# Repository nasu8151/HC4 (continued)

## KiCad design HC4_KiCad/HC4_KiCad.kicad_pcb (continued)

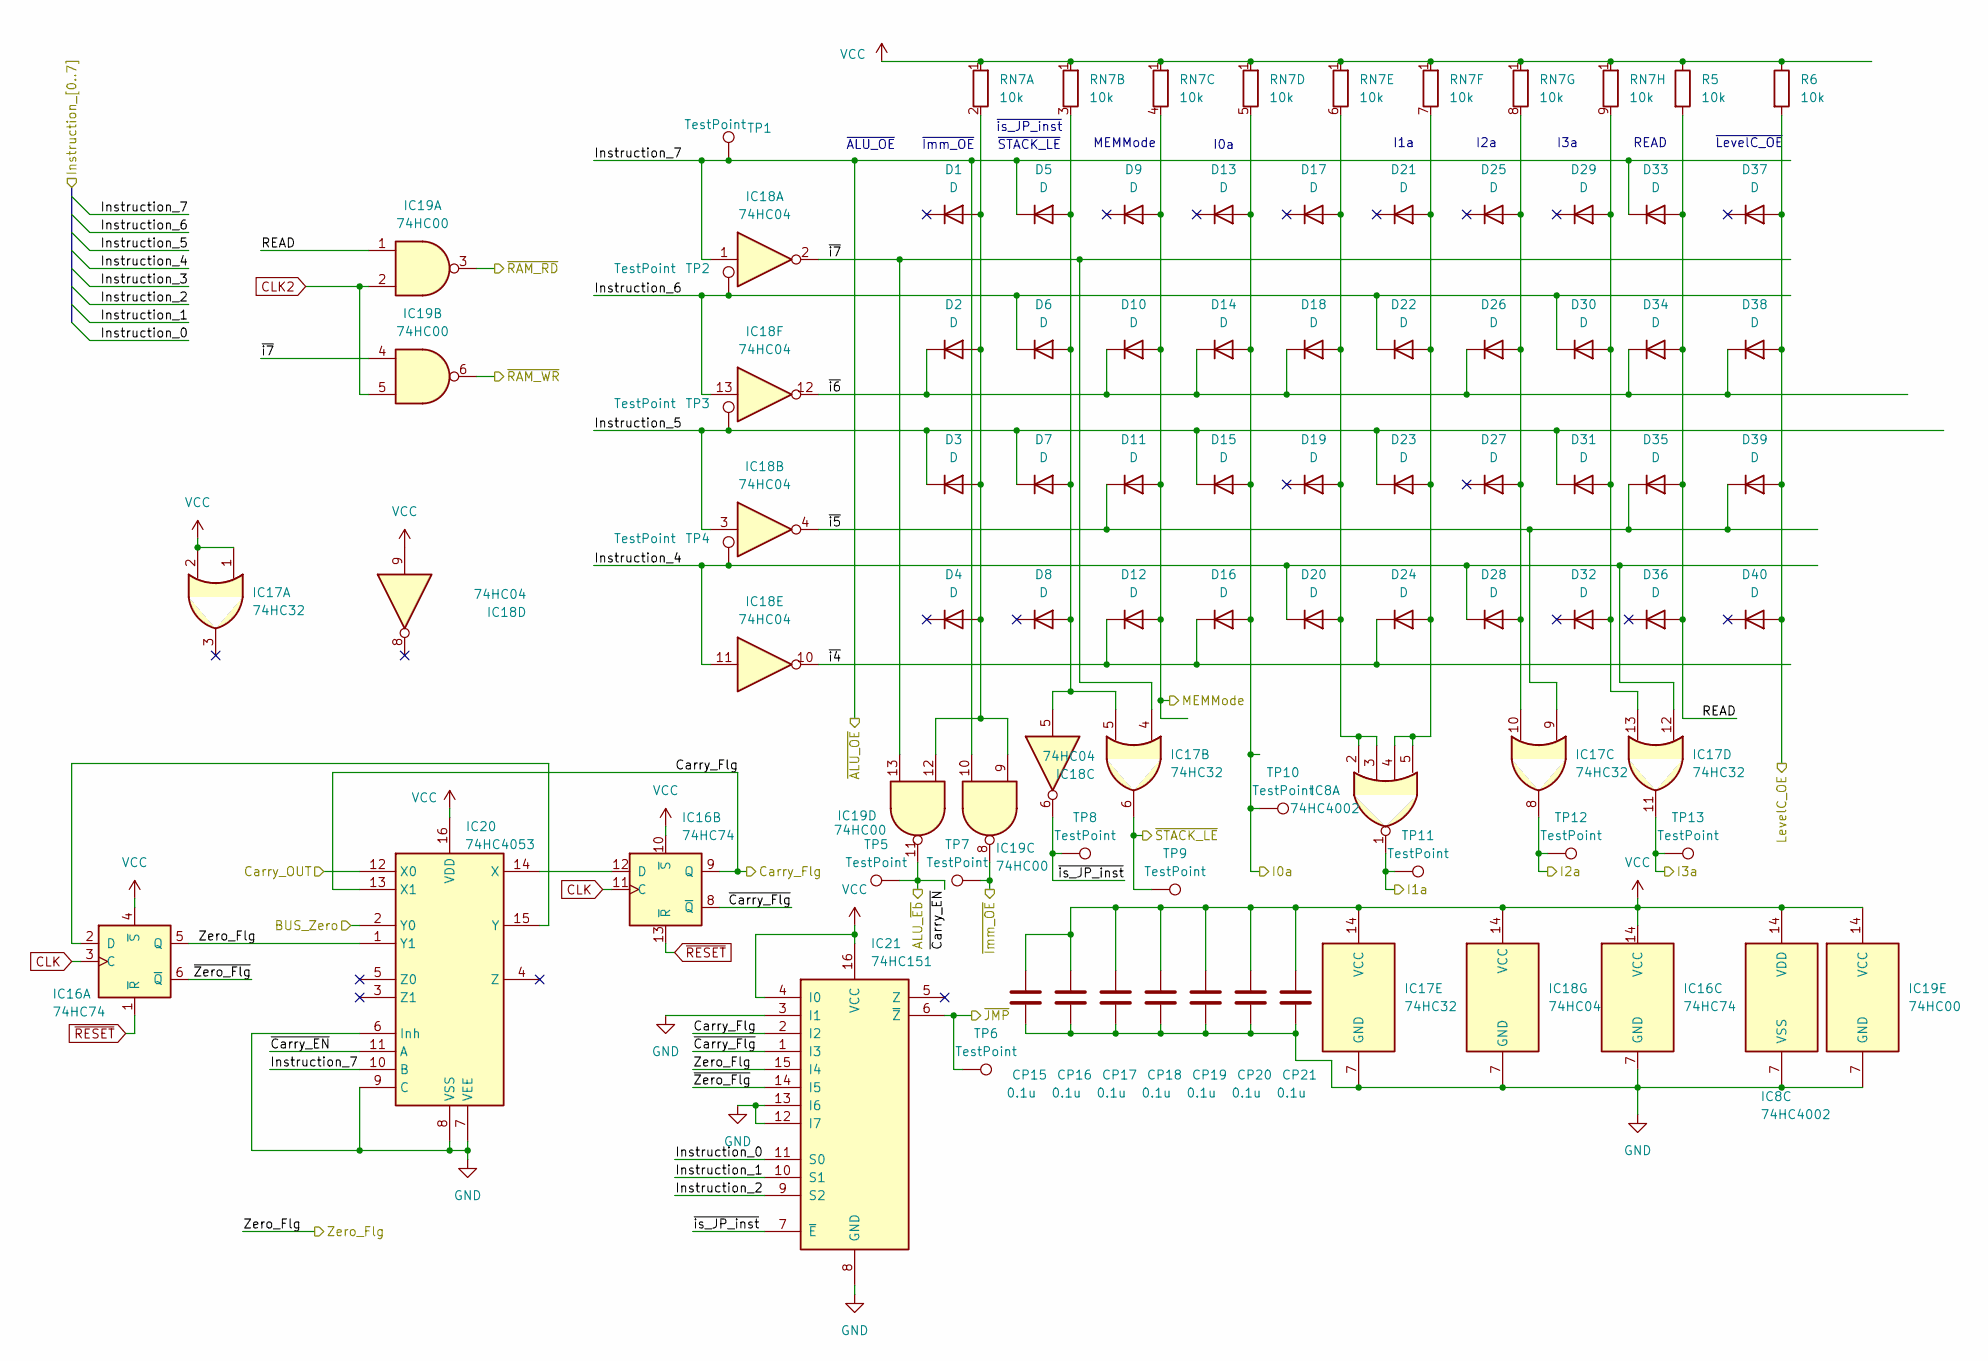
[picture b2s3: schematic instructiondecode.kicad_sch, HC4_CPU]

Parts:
CP15, CP16, CP17, CP18, CP19, CP20, CP21: 0.1u; C_0603_1608Metric
D1, D2, D3, D4, D5, D6, D7, D8, D9, D10, D11, D12, D13, D14, D15, D16, D17, D18, D19, D20, D21, D22, D23, D24, D25, D26, D27, D28, D29, D30, D31, D32, D33, D34, D35, D36, D37, D38, D39, D40: D; D_SOD-323_HandSoldering
IC8: 74HC4002; DIP-14_W7.62mm
IC16: 74HC74; DIP-14_W7.62mm
IC17: 74HC32; DIP-14_W7.62mm
IC18: 74HC04; DIP-14_W7.62mm
IC19: 74HC00; DIP-14_W7.62mm
IC20: 74HC4053; DIP-16_W7.62mm
IC21: 74HC151; DIP-16_W7.62mm
R5, R6: 10k; R_0603_1608Metric
RN7: 10k; R_Array_SIP9
TP1, TP2, TP3, TP4, TP5, TP6, TP7, TP8, TP9, TP10, TP11, TP12, TP13: TestPoint; TestPoint_THTPad_1.0x1.0mm_Drill0.5mm

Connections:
/ALU/Carry_IN: D13.2 (A_2), D14.2 (A), D15.2 (A), D16.2 (A), RN7.5 (R4.2), TP10.1 (1_1); also elsewhere on the board
/ALU/Carry_OUT: IC20.12 (X0); also elsewhere on the board
/ALU/I1a: IC8.1, TP11.1 (1_1); also elsewhere on the board
/ALU/I2a: IC17.8, TP12.1 (1_1); also elsewhere on the board
/ALU/I3a: IC17.11, TP13.1 (1_1); also elsewhere on the board
/Address BUS/Instruction_0: IC21.11 (S0); also elsewhere on the board
/Address BUS/Instruction_1: IC21.10 (S1); also elsewhere on the board
/Address BUS/Instruction_2: IC21.9 (S2); also elsewhere on the board
/Address BUS/Instruction_4: D20.1 (K), D28.1 (K), IC17.12, IC18.11, TP4.1 (1_1); also elsewhere on the board
/Address BUS/Instruction_5: D3.1 (K), D7.1 (K), D15.1 (K), D23.1 (K), D31.1 (K), IC18.3, TP3.1 (1_1); also elsewhere on the board
/Address BUS/Instruction_6: D6.1 (K), D22.1 (K), D30.1 (K), IC18.13, TP2.1 (1_1); also elsewhere on the board
/Address BUS/Instruction_7: D5.1 (K), D33.1 (K), IC18.1, IC19.10, IC20.10 (B), TP1.1 (1_1); also elsewhere on the board
/Address BUS/MEMMode: D9.2 (A_2), D10.2 (A), D11.2 (A), D12.2 (A), RN7.4 (R3.2); also elsewhere on the board
/Data BUS/BUS_Zero: IC20.2 (Y0); also elsewhere on the board
/Data BUS/Level_C_OE: D37.2 (A_2), D38.2 (A), D39.2 (A), D40.2 (A_2), R6.2; also elsewhere on the board
/Data BUS/~Immediate_OE: IC19.8, TP7.1 (1_1); also elsewhere on the board
/Data BUS/~RD: IC19.3; also elsewhere on the board
/Data BUS/~WR: IC19.6; also elsewhere on the board
/Instruction Decoder/Carry_Flg: IC16.9 (Q), IC20.13 (X1), IC21.2 (I2); also elsewhere on the board
/Instruction Decoder/READ: D33.2 (A), D34.2 (A), D35.2 (A), D36.2 (A_2), IC19.1, R5.2
/Instruction Decoder/Zero_Flg: IC16.5 (Q), IC20.1 (Y1), IC21.15 (I4); also elsewhere on the board
/Instruction Decoder/~Carry_EN: IC19.11, IC20.11 (A), TP5.1 (1_1); also elsewhere on the board
/Instruction Decoder/~Carry_Flg: IC16.8 (~Q), IC21.1 (I3)
/Instruction Decoder/~JMP: IC21.6 (~Z), TP6.1 (1_1); also elsewhere on the board
/Instruction Decoder/~STACK_LE: IC17.6, TP9.1 (1_1); also elsewhere on the board
/Instruction Decoder/~Zero_Flg: IC16.6 (~Q), IC21.14 (I5)
/Instruction Decoder/~i4: D12.1 (K), D16.1 (K), D24.1 (K), IC18.10
/Instruction Decoder/~i5: D11.1 (K), D35.1 (K), D39.1 (K), IC17.9, IC18.4
/Instruction Decoder/~i6: D2.1 (K), D10.1 (K), D14.1 (K), D18.1 (K), D26.1 (K), D34.1 (K), D38.1 (K), IC18.12
/Instruction Decoder/~i7: IC17.4, IC18.2, IC19.4, IC19.13
/Instruction Decoder/~is_JP_inst: IC18.6, IC21.7 (~E), TP8.1 (1_1)
CLK: IC16.3 (C), IC16.11 (C); also elsewhere on the board
CLK2: IC19.2, IC19.5; also elsewhere on the board
GND: CP15.2, CP16.2, CP17.2, CP18.2, CP19.2, CP20.2, CP21.2, IC8.7 (VSS), IC16.7 (GND), IC17.7 (GND), IC18.7 (GND), IC19.7 (GND), IC20.6 (Inh), IC20.7 (VEE), IC20.8 (VSS), IC20.9 (C), IC21.3 (I1), IC21.8 (GND), IC21.12 (I7), IC21.13 (I6); also elsewhere on the board
unnamed: D1.2 (A_2), D2.2 (A), D3.2 (A), D4.2 (A_2), IC19.9, IC19.12, RN7.2 (R1.2)
unnamed: D5.2 (A), D6.2 (A), D7.2 (A), D8.2 (A_2), IC17.5, IC18.5, RN7.3 (R2.2)
unnamed: D17.2 (A_2), D18.2 (A), D19.2 (A_2), D20.2 (A), IC8.2, IC8.3, RN7.6 (R5.2)
unnamed: D21.2 (A_2), D22.2 (A), D23.2 (A), D24.2 (A), IC8.4, IC8.5, RN7.7 (R6.2)
unnamed: D25.2 (A_2), D26.2 (A), D27.2 (A_2), D28.2 (A), IC17.10, RN7.8 (R7.2)
unnamed: D29.2 (A_2), D30.2 (A), D31.2 (A), D32.2 (A_2), IC17.13, RN7.9 (R8.2)
unnamed: IC16.2 (D), IC20.15 (Y)
unnamed: IC16.12 (D), IC20.14 (X)
VCC: CP15.1, CP16.1, CP17.1, CP18.1, CP19.1, CP20.1, CP21.1, IC8.14 (VDD), IC16.4 (~S), IC16.10 (~S), IC16.14 (VCC), IC17.1, IC17.2, IC17.14 (VCC), IC18.9, IC18.14 (VCC), IC19.14 (VCC), IC20.16 (VDD), IC21.4 (I0), IC21.16 (VCC), R5.1, R6.1, RN7.1 (R1); also elsewhere on the board
~RESET: IC16.1 (~R), IC16.13 (~R); also elsewhere on the board

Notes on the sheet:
I2a
I0a
~{Imm_OE}
~{LevelC_OE}
~{ALU_OE}
~{STACK_LE}
I3a
READ
MEMMode
I1a
~{is_JP_inst}

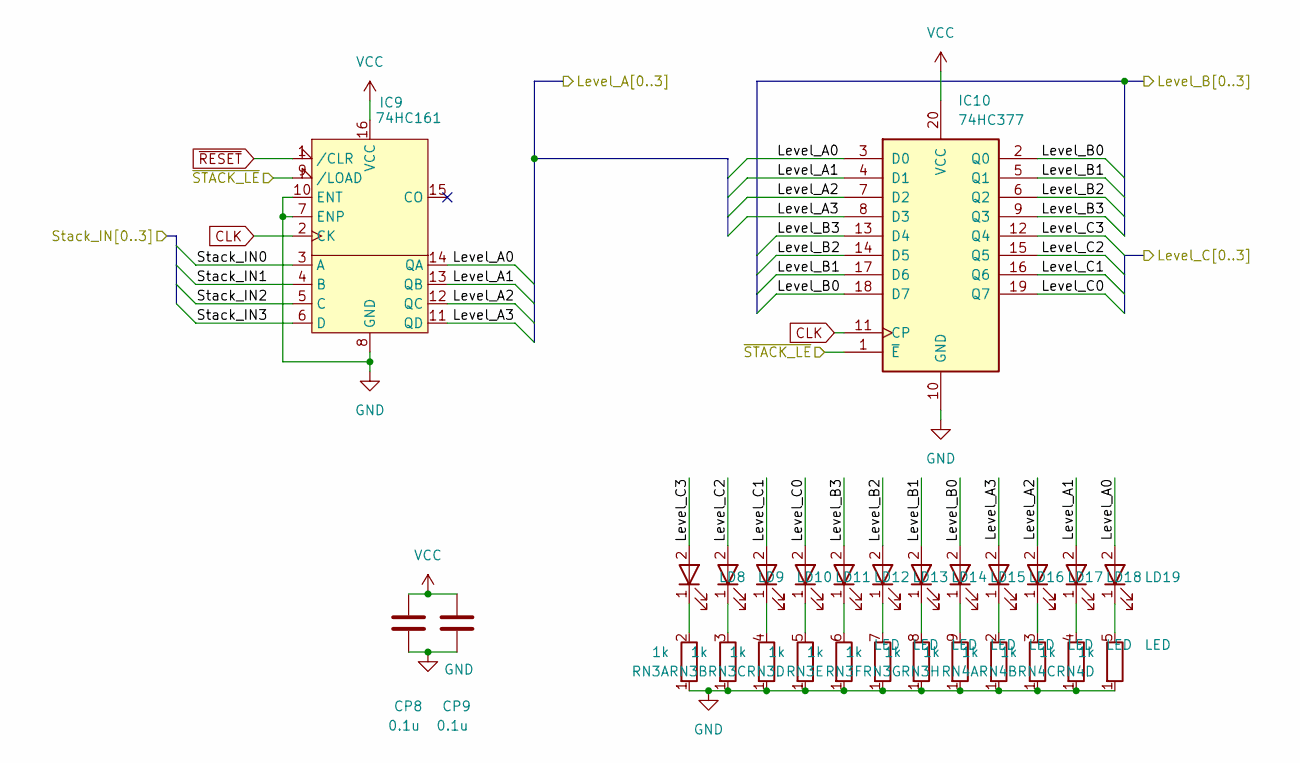
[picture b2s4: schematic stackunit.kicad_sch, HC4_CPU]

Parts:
CP8, CP9: 0.1u; C_0603_1608Metric
IC9: 74HC161; DIP-16_W7.62mm
IC10: 74HC377; DIP-20_W7.62mm
LD8, LD9, LD10, LD11, LD12, LD13, LD14, LD15, LD16, LD17, LD18, LD19: LED; LED_Rectangular_W5.0mm_H2.0mm
RN3, RN4: 1k; R_Array_SIP9

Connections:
/ALU/ALU_in_A0: IC9.14 (QA), IC10.3 (D0), LD19.2; also elsewhere on the board
/ALU/ALU_in_A1: IC9.13 (QB), IC10.4 (D1), LD18.2; also elsewhere on the board
/ALU/ALU_in_A2: IC9.12 (QC), IC10.7 (D2), LD17.2; also elsewhere on the board
/ALU/ALU_in_A3: IC9.11 (QD), IC10.8 (D3), LD16.2; also elsewhere on the board
/ALU/ALU_in_B0: IC10.2 (Q0), IC10.18 (D7), LD15.2; also elsewhere on the board
/ALU/ALU_in_B1: IC10.5 (Q1), IC10.17 (D6), LD14.2; also elsewhere on the board
/ALU/ALU_in_B2: IC10.6 (Q2), IC10.14 (D5), LD13.2; also elsewhere on the board
/ALU/ALU_in_B3: IC10.9 (Q3), IC10.13 (D4), LD12.2; also elsewhere on the board
/Data BUS/Databus0: IC9.3 (A); also elsewhere on the board
/Data BUS/Databus1: IC9.4 (B); also elsewhere on the board
/Data BUS/Databus2: IC9.5 (C); also elsewhere on the board
/Data BUS/Databus3: IC9.6 (D); also elsewhere on the board
/Data BUS/Level_C0: IC10.19 (Q7), LD11.2; also elsewhere on the board
/Data BUS/Level_C1: IC10.16 (Q6), LD10.2; also elsewhere on the board
/Data BUS/Level_C2: IC10.15 (Q5), LD9.2; also elsewhere on the board
/Data BUS/Level_C3: IC10.12 (Q4), LD8.2; also elsewhere on the board
/Instruction Decoder/~STACK_LE: IC9.9 (/LOAD), IC10.1 (~E); also elsewhere on the board
CLK: IC9.2 (CK), IC10.11 (CP); also elsewhere on the board
GND: CP8.2, CP9.2, IC9.7 (ENP), IC9.8 (GND), IC9.10 (ENT), IC10.10 (GND), RN3.1 (R1), RN4.1 (R1); also elsewhere on the board
unnamed: LD8.1 (K_1), RN3.2 (R1.2)
unnamed: LD9.1 (K_1), RN3.3 (R2.2)
unnamed: LD10.1 (K_1), RN3.4 (R3.2)
unnamed: LD11.1 (K_1), RN3.5 (R4.2)
unnamed: LD12.1 (K_1), RN3.6 (R5.2)
unnamed: LD13.1 (K_1), RN3.7 (R6.2)
unnamed: LD14.1 (K_1), RN3.8 (R7.2)
unnamed: LD15.1 (K_1), RN3.9 (R8.2)
unnamed: LD16.1 (K_1), RN4.2 (R1.2)
unnamed: LD17.1 (K_1), RN4.3 (R2.2)
unnamed: LD18.1 (K_1), RN4.4 (R3.2)
unnamed: LD19.1 (K_1), RN4.5 (R4.2)
VCC: CP8.1, CP9.1, IC9.16 (VCC), IC10.20 (VCC); also elsewhere on the board
~RESET: IC9.1 (/CLR); also elsewhere on the board

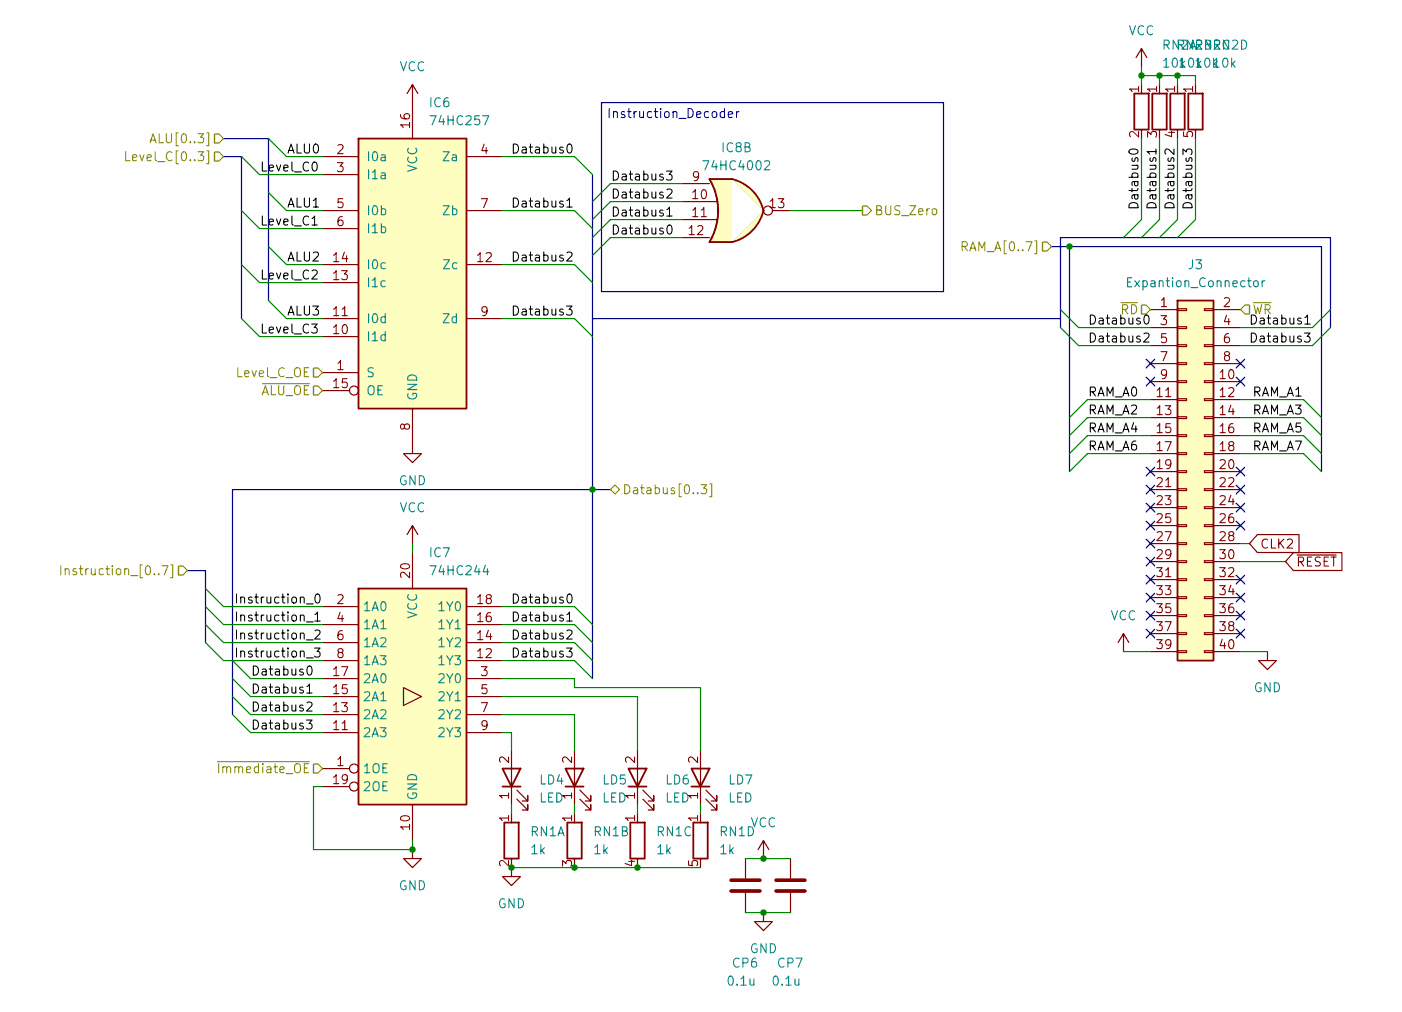
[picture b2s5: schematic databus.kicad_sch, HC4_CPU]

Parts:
CP6, CP7: 0.1u; C_0603_1608Metric
IC6: 74HC257; DIP-16_W7.62mm
IC7: 74HC244; DIP-20_W7.62mm
IC8: 74HC4002; DIP-14_W7.62mm
J3: Expantion_Connector; PinHeader_2x20_P2.54mm_Vertical
LD4, LD5, LD6, LD7: LED; LED_Rectangular_W5.0mm_H2.0mm
RN1: 1k; R_Array_SIP5
RN2: 10k; R_Array_SIP5

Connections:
/ALU/ALU_OUT0: IC6.2 (I0a); also elsewhere on the board
/ALU/ALU_OUT1: IC6.5 (I0b); also elsewhere on the board
/ALU/ALU_OUT2: IC6.14 (I0c); also elsewhere on the board
/ALU/ALU_OUT3: IC6.11 (I0d); also elsewhere on the board
/Address BUS/Instruction_0: IC7.2 (1A0); also elsewhere on the board
/Address BUS/Instruction_1: IC7.4 (1A1); also elsewhere on the board
/Address BUS/Instruction_2: IC7.6 (1A2); also elsewhere on the board
/Address BUS/Instruction_3: IC7.8 (1A3); also elsewhere on the board
/Address BUS/Instruction_7: IC6.15 (OE); also elsewhere on the board
/Address BUS/RAM_A0: J3.11; also elsewhere on the board
/Address BUS/RAM_A1: J3.12; also elsewhere on the board
/Address BUS/RAM_A2: J3.13; also elsewhere on the board
/Address BUS/RAM_A3: J3.14; also elsewhere on the board
/Address BUS/RAM_A4: J3.15; also elsewhere on the board
/Address BUS/RAM_A5: J3.16; also elsewhere on the board
/Address BUS/RAM_A6: J3.17; also elsewhere on the board
/Address BUS/RAM_A7: J3.18; also elsewhere on the board
/Data BUS/BUS_Zero: IC8.13; also elsewhere on the board
/Data BUS/Databus0: IC6.4 (Za), IC7.17 (2A0), IC7.18 (1Y0), IC8.12, J3.3, RN2.2 (R1.2); also elsewhere on the board
/Data BUS/Databus1: IC6.7 (Zb), IC7.15 (2A1), IC7.16 (1Y1), IC8.11, J3.4, RN2.3 (R2.2); also elsewhere on the board
/Data BUS/Databus2: IC6.12 (Zc), IC7.13 (2A2), IC7.14 (1Y2), IC8.10, J3.5, RN2.4 (R3.2); also elsewhere on the board
/Data BUS/Databus3: IC6.9 (Zd), IC7.11 (2A3), IC7.12 (1Y3), IC8.9, J3.6, RN2.5 (R4.2); also elsewhere on the board
/Data BUS/Level_C0: IC6.3 (I1a); also elsewhere on the board
/Data BUS/Level_C1: IC6.6 (I1b); also elsewhere on the board
/Data BUS/Level_C2: IC6.13 (I1c); also elsewhere on the board
/Data BUS/Level_C3: IC6.10 (I1d); also elsewhere on the board
/Data BUS/Level_C_OE: IC6.1 (S); also elsewhere on the board
/Data BUS/~Immediate_OE: IC7.1 (1OE); also elsewhere on the board
/Data BUS/~RD: J3.1; also elsewhere on the board
/Data BUS/~WR: J3.2; also elsewhere on the board
CLK2: J3.28; also elsewhere on the board
GND: CP6.2, CP7.2, IC6.8 (GND), IC7.10 (GND), IC7.19 (2OE), J3.40, RN1.2 (R1.2), RN1.3 (R2.2), RN1.4 (R3.2), RN1.5 (R4.2); also elsewhere on the board
unnamed: IC7.3 (2Y0), LD7.2
unnamed: IC7.5 (2Y1), LD6.2
unnamed: IC7.7 (2Y2), LD5.2
unnamed: IC7.9 (2Y3), LD4.2
VCC: CP6.1, CP7.1, IC6.16 (VCC), IC7.20 (VCC), J3.39, RN2.1 (R1); also elsewhere on the board
~RESET: J3.30; also elsewhere on the board

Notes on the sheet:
Instruction_Decoder

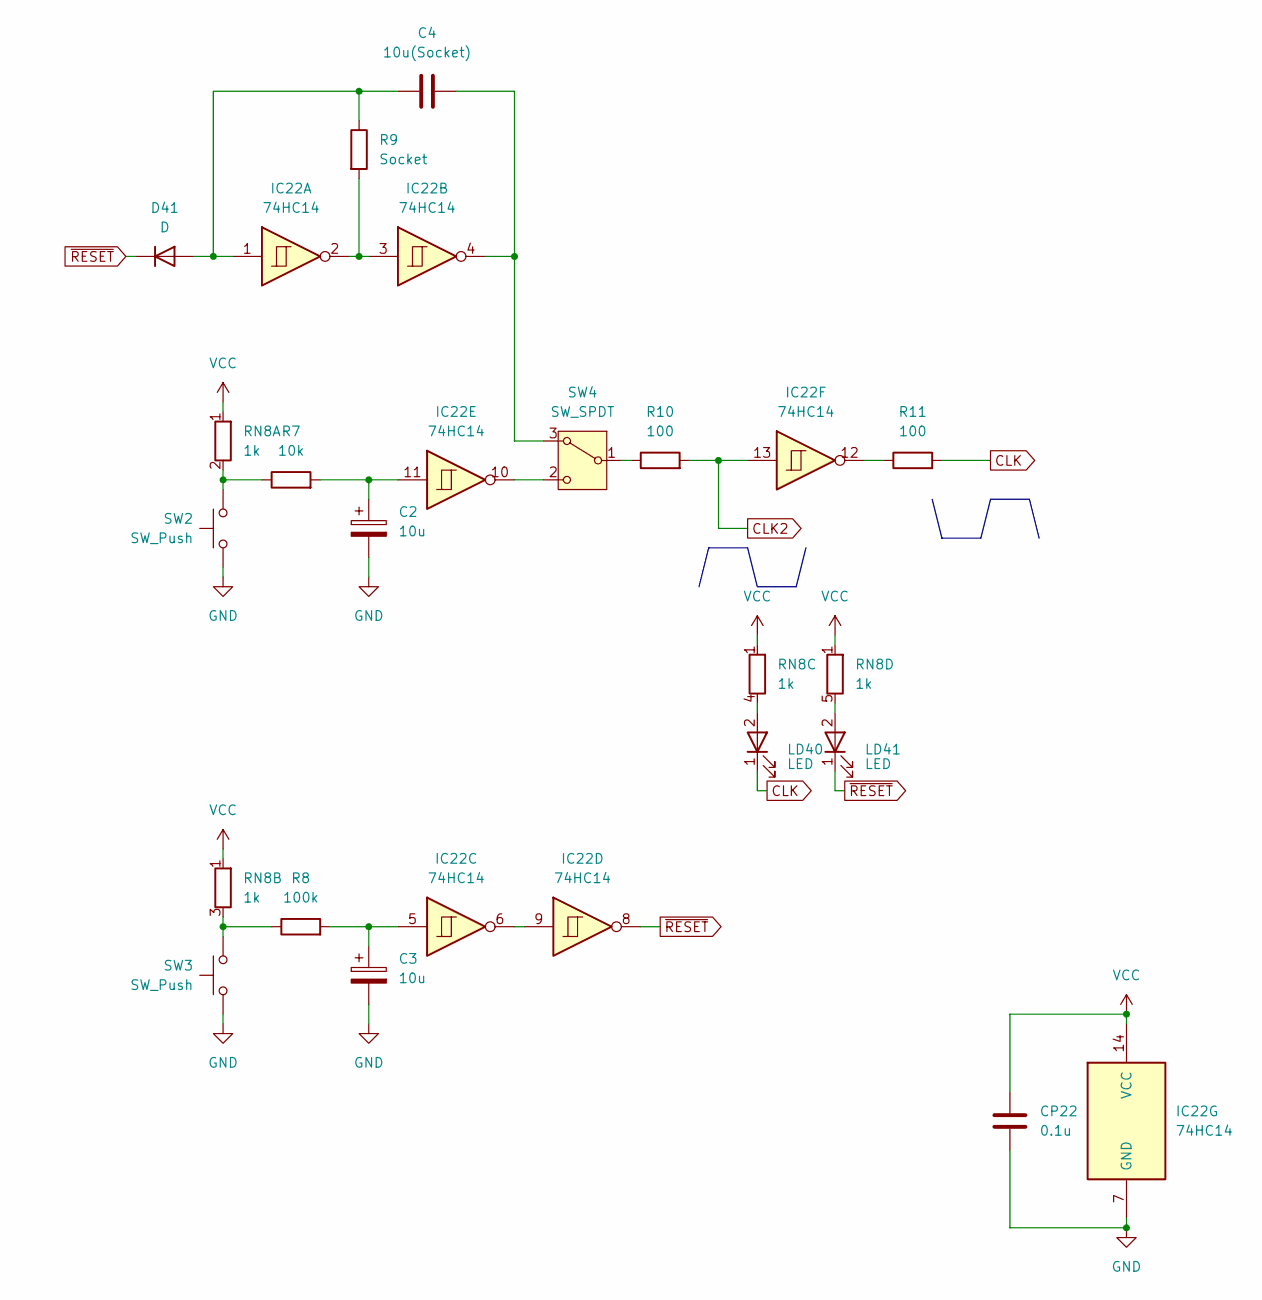
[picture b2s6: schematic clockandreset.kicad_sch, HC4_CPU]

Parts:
C2, C3: 10u; CP_Radial_D5.0mm_P2.50mm
C4: 10u(Socket); C_Radial_D6.3mm_H5.0mm_P2.50mm
CP22: 0.1u; C_0603_1608Metric
D41: D; D_SOD-323_HandSoldering
IC22: 74HC14; DIP-14_W7.62mm
LD40, LD41: LED; LED_Rectangular_W5.0mm_H2.0mm
R7: 10k; R_0603_1608Metric
R8: 100k; R_0603_1608Metric
R9: Socket; R_Axial_DIN0207_L6.3mm_D2.5mm_P10.16mm_Horizontal
R10, R11: 100; R_0603_1608Metric
RN8: 1k; R_Array_SIP5
SW2, SW3: SW_Push; SW_PUSH_6mm
SW4: SW_SPDT; SW_Slide-03_Wuerth-WS-SLTV_10x2.5x6.4_P2.54mm

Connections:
CLK: LD40.1 (K_1), R11.2; also elsewhere on the board
CLK2: IC22.13, R10.2; also elsewhere on the board
GND: C2.2, C3.2, CP22.2, IC22.7 (GND), SW2.1, SW3.1; also elsewhere on the board
unnamed: C2.1, IC22.11, R7.2
unnamed: C3.1, IC22.5, R8.2
unnamed: C4.1, D41.2 (A), IC22.1, R9.1
unnamed: IC22.2, IC22.3, R9.2
unnamed: IC22.6, IC22.9
unnamed: IC22.12, R11.1
unnamed: R7.1, RN8.2 (R1.2), SW2.2
unnamed: R8.1, RN8.3 (R2.2), SW3.2
unnamed: LD40.2, RN8.4 (R3.2)
unnamed: LD41.2, RN8.5 (R4.2)
unnamed: C4.2, IC22.4, SW4.3 (A)
unnamed: R10.1, SW4.1 (B)
unnamed: IC22.10, SW4.2 (C)
VCC: CP22.1, IC22.14 (VCC), RN8.1 (R1); also elsewhere on the board
~RESET: D41.1 (K), IC22.8, LD41.1 (K_1); also elsewhere on the board

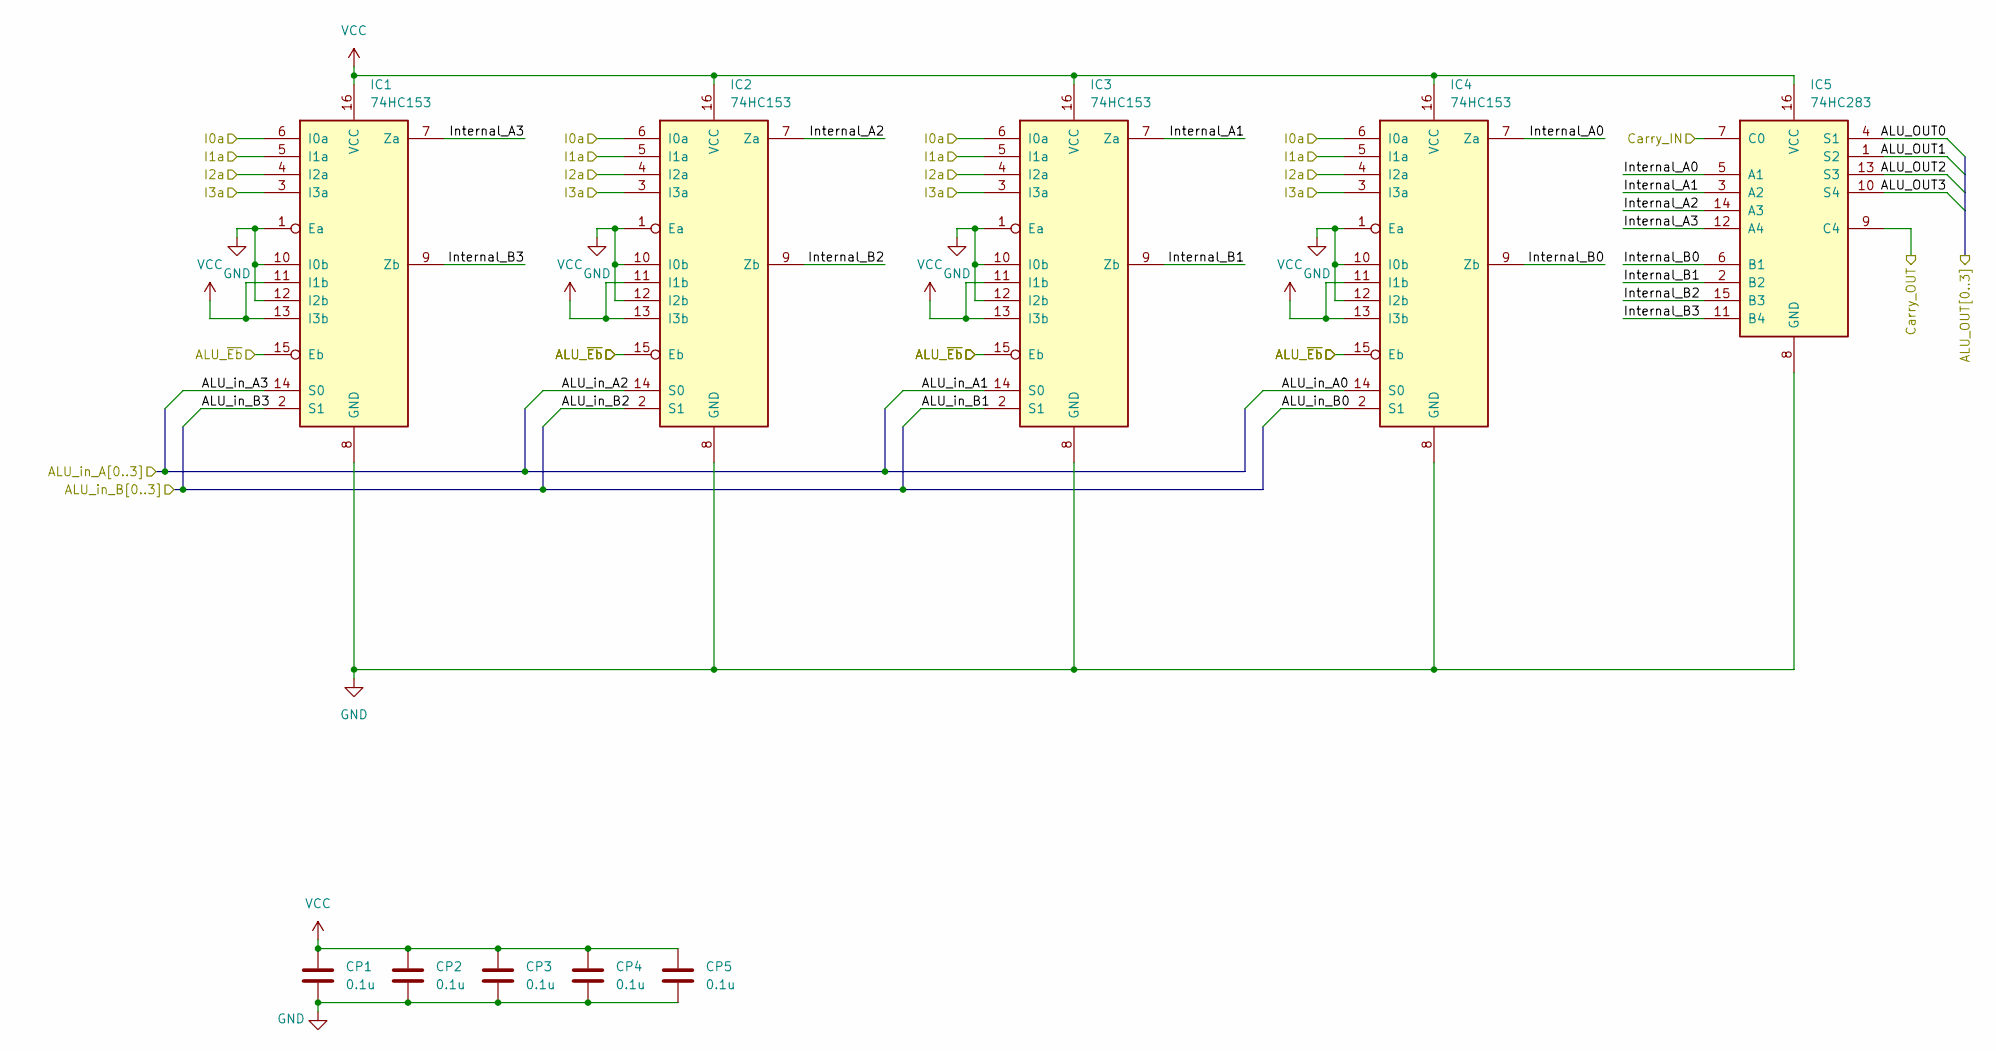
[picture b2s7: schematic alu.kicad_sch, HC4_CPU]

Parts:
CP1, CP2, CP3, CP4, CP5: 0.1u; C_0603_1608Metric
IC1, IC2, IC3, IC4: 74HC153; DIP-16_W7.62mm
IC5: 74HC283; DIP-16_W7.62mm

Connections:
/ALU/ALU_OUT0: IC5.4 (S1); also elsewhere on the board
/ALU/ALU_OUT1: IC5.1 (S2); also elsewhere on the board
/ALU/ALU_OUT2: IC5.13 (S3); also elsewhere on the board
/ALU/ALU_OUT3: IC5.10 (S4); also elsewhere on the board
/ALU/ALU_in_A0: IC4.14 (S0); also elsewhere on the board
/ALU/ALU_in_A1: IC3.14 (S0); also elsewhere on the board
/ALU/ALU_in_A2: IC2.14 (S0); also elsewhere on the board
/ALU/ALU_in_A3: IC1.14 (S0); also elsewhere on the board
/ALU/ALU_in_B0: IC4.2 (S1); also elsewhere on the board
/ALU/ALU_in_B1: IC3.2 (S1); also elsewhere on the board
/ALU/ALU_in_B2: IC2.2 (S1); also elsewhere on the board
/ALU/ALU_in_B3: IC1.2 (S1); also elsewhere on the board
/ALU/Carry_IN: IC1.6 (I0a), IC2.6 (I0a), IC3.6 (I0a), IC4.6 (I0a), IC5.7 (C0); also elsewhere on the board
/ALU/Carry_OUT: IC5.9 (C4); also elsewhere on the board
/ALU/I1a: IC1.5 (I1a), IC2.5 (I1a), IC3.5 (I1a), IC4.5 (I1a); also elsewhere on the board
/ALU/I2a: IC1.4 (I2a), IC2.4 (I2a), IC3.4 (I2a), IC4.4 (I2a); also elsewhere on the board
/ALU/I3a: IC1.3 (I3a), IC2.3 (I3a), IC3.3 (I3a), IC4.3 (I3a); also elsewhere on the board
/ALU/Internal_A0: IC4.7 (Za), IC5.5 (A1)
/ALU/Internal_A1: IC3.7 (Za), IC5.3 (A2)
/ALU/Internal_A2: IC2.7 (Za), IC5.14 (A3)
/ALU/Internal_A3: IC1.7 (Za), IC5.12 (A4)
/ALU/Internal_B0: IC4.9 (Zb), IC5.6 (B1)
/ALU/Internal_B1: IC3.9 (Zb), IC5.2 (B2)
/ALU/Internal_B2: IC2.9 (Zb), IC5.15 (B3)
/ALU/Internal_B3: IC1.9 (Zb), IC5.11 (B4)
/Instruction Decoder/~Carry_EN: IC1.15 (Eb), IC2.15 (Eb), IC3.15 (Eb), IC4.15 (Eb); also elsewhere on the board
GND: CP1.2, CP2.2, CP3.2, CP4.2, CP5.2, IC1.1 (Ea), IC1.8 (GND), IC1.10 (I0b), IC1.12 (I2b), IC2.1 (Ea), IC2.8 (GND), IC2.10 (I0b), IC2.12 (I2b), IC3.1 (Ea), IC3.8 (GND), IC3.10 (I0b), IC3.12 (I2b), IC4.1 (Ea), IC4.8 (GND), IC4.10 (I0b), IC4.12 (I2b), IC5.8 (GND); also elsewhere on the board
VCC: CP1.1, CP2.1, CP3.1, CP4.1, CP5.1, IC1.11 (I1b), IC1.13 (I3b), IC1.16 (VCC), IC2.11 (I1b), IC2.13 (I3b), IC2.16 (VCC), IC3.11 (I1b), IC3.13 (I3b), IC3.16 (VCC), IC4.11 (I1b), IC4.13 (I3b), IC4.16 (VCC), IC5.16 (VCC); also elsewhere on the board

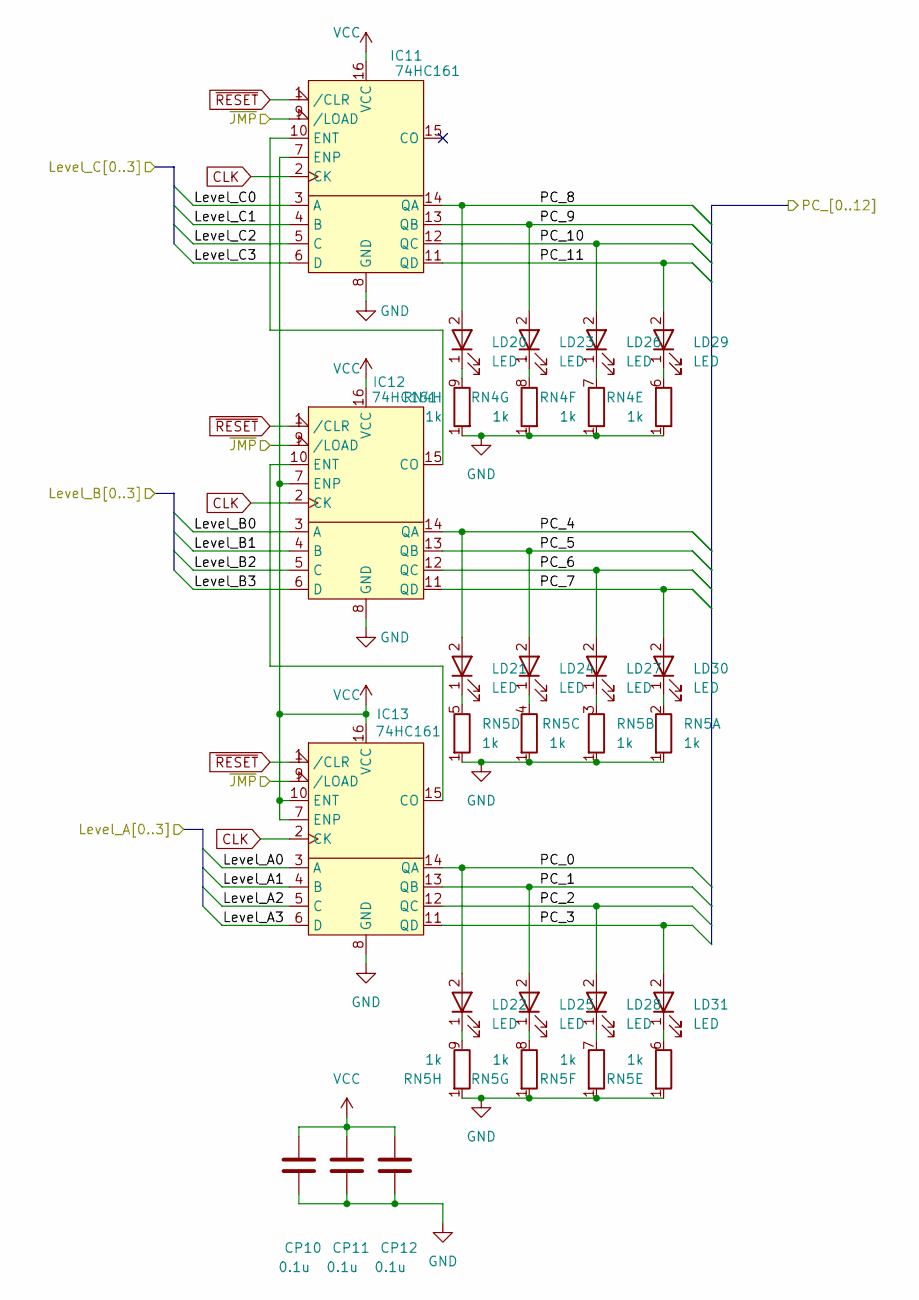
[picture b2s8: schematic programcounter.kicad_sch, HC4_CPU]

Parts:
CP10, CP11, CP12: 0.1u; C_0603_1608Metric
IC11, IC12, IC13: 74HC161; DIP-16_W7.62mm
LD20, LD21, LD22, LD23, LD24, LD25, LD26, LD27, LD28, LD29, LD30, LD31: LED; LED_Rectangular_W5.0mm_H2.0mm
RN4, RN5: 1k; R_Array_SIP9

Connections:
/ALU/ALU_in_A0: IC13.3 (A); also elsewhere on the board
/ALU/ALU_in_A1: IC13.4 (B); also elsewhere on the board
/ALU/ALU_in_A2: IC13.5 (C); also elsewhere on the board
/ALU/ALU_in_A3: IC13.6 (D); also elsewhere on the board
/ALU/ALU_in_B0: IC12.3 (A); also elsewhere on the board
/ALU/ALU_in_B1: IC12.4 (B); also elsewhere on the board
/ALU/ALU_in_B2: IC12.5 (C); also elsewhere on the board
/ALU/ALU_in_B3: IC12.6 (D); also elsewhere on the board
/Data BUS/Level_C0: IC11.3 (A); also elsewhere on the board
/Data BUS/Level_C1: IC11.4 (B); also elsewhere on the board
/Data BUS/Level_C2: IC11.5 (C); also elsewhere on the board
/Data BUS/Level_C3: IC11.6 (D); also elsewhere on the board
/Instruction Decoder/~JMP: IC11.9 (/LOAD), IC12.9 (/LOAD), IC13.9 (/LOAD); also elsewhere on the board
/Program Counter/PC_0: IC13.14 (QA), LD22.2; also elsewhere on the board
/Program Counter/PC_1: IC13.13 (QB), LD25.2; also elsewhere on the board
/Program Counter/PC_2: IC13.12 (QC), LD28.2; also elsewhere on the board
/Program Counter/PC_3: IC13.11 (QD), LD31.2; also elsewhere on the board
/Program Counter/PC_4: IC12.14 (QA), LD21.2; also elsewhere on the board
/Program Counter/PC_5: IC12.13 (QB), LD24.2; also elsewhere on the board
/Program Counter/PC_6: IC12.12 (QC), LD27.2; also elsewhere on the board
/Program Counter/PC_7: IC12.11 (QD), LD30.2; also elsewhere on the board
/Program Counter/PC_8: IC11.14 (QA), LD20.2; also elsewhere on the board
/Program Counter/PC_9: IC11.13 (QB), LD23.2; also elsewhere on the board
/Program Counter/PC_10: IC11.12 (QC), LD26.2; also elsewhere on the board
/Program Counter/PC_11: IC11.11 (QD), LD29.2; also elsewhere on the board
CLK: IC11.2 (CK), IC12.2 (CK), IC13.2 (CK); also elsewhere on the board
GND: CP10.2, CP11.2, CP12.2, IC11.8 (GND), IC12.8 (GND), IC13.8 (GND), RN4.1 (R1), RN5.1 (R1); also elsewhere on the board
unnamed: IC11.10 (ENT), IC12.15 (CO)
unnamed: IC12.10 (ENT), IC13.15 (CO)
unnamed: LD20.1 (K_1), RN4.9 (R8.2)
unnamed: LD21.1 (K_1), RN5.5 (R4.2)
unnamed: LD22.1 (K_1), RN5.9 (R8.2)
unnamed: LD23.1 (K_1), RN4.8 (R7.2)
unnamed: LD24.1 (K_1), RN5.4 (R3.2)
unnamed: LD25.1 (K_1), RN5.8 (R7.2)
unnamed: LD26.1 (K_1), RN4.7 (R6.2)
unnamed: LD27.1 (K_1), RN5.3 (R2.2)
unnamed: LD28.1 (K_1), RN5.7 (R6.2)
unnamed: LD29.1 (K_1), RN4.6 (R5.2)
unnamed: LD30.1 (K_1), RN5.2 (R1.2)
unnamed: LD31.1 (K_1), RN5.6 (R5.2)
VCC: CP10.1, CP11.1, CP12.1, IC11.7 (ENP), IC11.16 (VCC), IC12.7 (ENP), IC12.16 (VCC), IC13.7 (ENP), IC13.10 (ENT), IC13.16 (VCC); also elsewhere on the board
~RESET: IC11.1 (/CLR), IC12.1 (/CLR), IC13.1 (/CLR); also elsewhere on the board

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
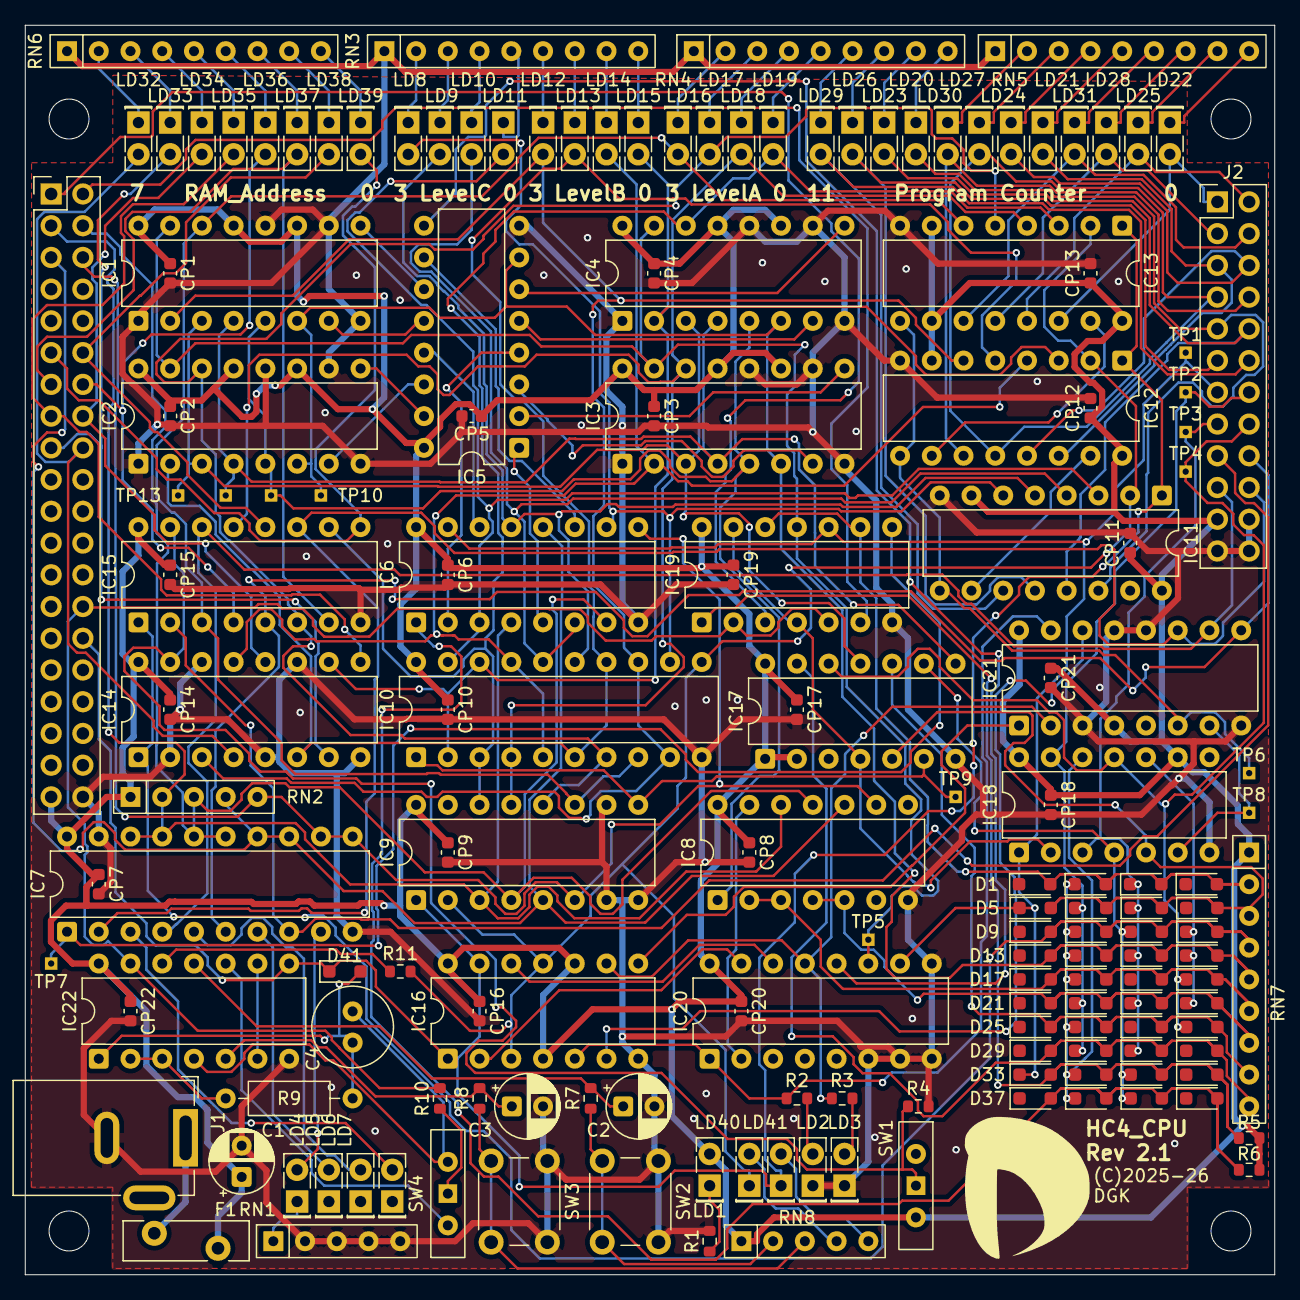
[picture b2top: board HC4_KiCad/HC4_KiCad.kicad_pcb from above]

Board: 2 copper layers, 100.0 x 100.0 mm, 174 parts (0 on the bottom side), 150 nets.
